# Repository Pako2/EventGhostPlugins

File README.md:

# [EventGhost](http://www.eventghost.net/) plugins.

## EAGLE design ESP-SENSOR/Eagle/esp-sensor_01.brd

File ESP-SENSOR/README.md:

# ESP-SENSOR - Temperaure & humidity sensor and remote-controlled electrical socket
This project is basically the same as the [ESP-SOCKET](https://github.com/Pako2/EventGhostPlugins/tree/master/ESP-SOCKET) project. The difference is only that a temperature and humidity sensor HTU-21D has been added.
Therefore, the original text [README.md](https://github.com/Pako2/EventGhostPlugins/tree/master/ESP-SOCKET/README.md) is fully valid also for this project (only the word "SENSOR" must be used everywhere instead of "SOCKET").

## Initial requirements
I realized that the potential of ESP8266 is very little used in the [ESP-SOCKET](https://github.com/Pako2/EventGhostPlugins/tree/master/ESP-SOCKET) project and that it should be very easy to use it more.
As a first possibility of improvement I was thinking of adding some sensor. I had the HTU-21D sensor at home, so it was the simplest thing for me to add the HTU-21D sensor.
Eventghost plugin should allow to set any number of significant levels.
If any of the levels are exceeded (and / or the value drops below), the corresponding event should be triggered.
A change of relay state must trigger an event in EventGhost too.

### What You Will Need 
### Hardware
An ESP-12 module with at least 32Mbit Flash (equals to 4MBytes)  
A HTU-21D module.

### Software
In contrast to the [ESP-SOCKET](https://github.com/Pako2/EventGhostPlugins/tree/master/ESP-SOCKET) project, one additional library was needed here:
* [HTU21D](https://github.com/enjoyneering/)  - an Arduino library for SHT21, HTU21D & Si70xx written by enjoyneering79

## How the development went
As can be seen from the pictures, this time I worked in two steps:  

1) The breadboard construction (I just added the HTU-21D module to a previously prepared breadboard)
2) Newly designed printed circuit board

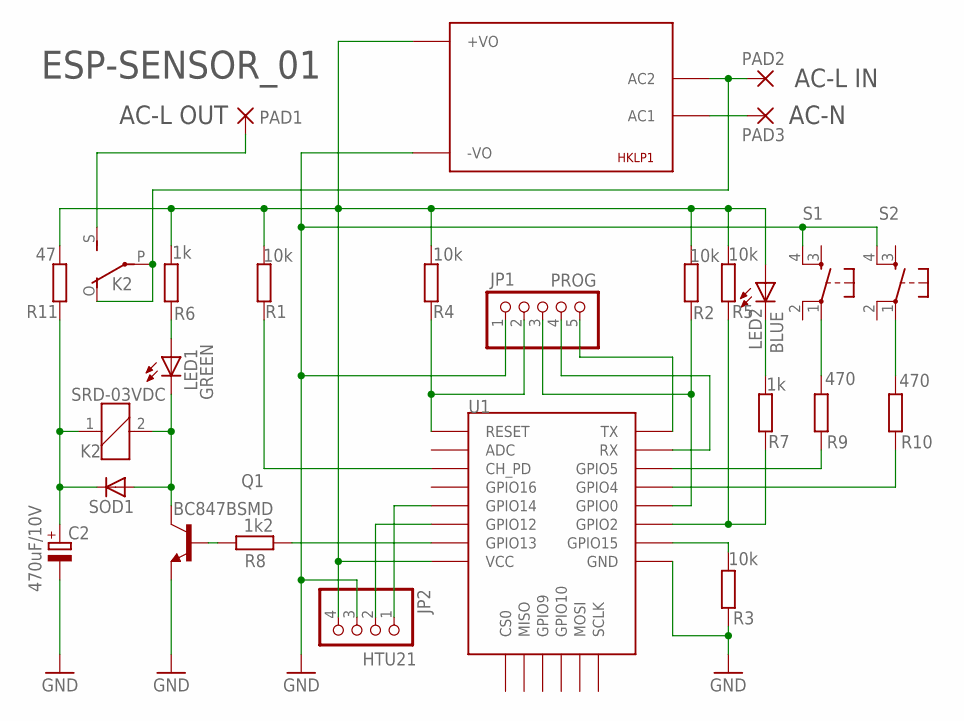
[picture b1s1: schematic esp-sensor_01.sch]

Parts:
C2: 470uF/10V; E3,5-8-B
HKLP1: HKLPM01
JP1: PROG; 1X05-2B
JP2: HTU21; 1X04
K2: SRD-03VDC; G5L-2B
LED1: GREEN; LED3MM-B
LED2: BLUE; LED3MM-B
PAD1, PAD2, PAD3: 3,17/1,1
Q1: BC847BSMD; SOT23
R1, R2, R3, R4, R5: 10k; M1206
R6, R7: 1k; M1206
R8: 1k2; M1206
R9, R10: 470; M1206
R11: 47; 0207/10-2B
S1, S2: DTS-6-B
SOD1: DIODE-MELF-MLL41; MELF-MLL41
U1: ESP12ESMD; ESP12E-SMD

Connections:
3V3: HKLP1.P$4 (+VO), JP2.4, LED2.A, R1.2, R2.2, R4.2, R5.2, R6.2, R11.2, U1.VCC
GND: C2.-, HKLP1.P$3 (-VO), JP1.1, JP2.3, Q1.2 (E), R3.1, S1.4, S2.4, U1.GND
unnamed: Q1.1 (B), R8.2
unnamed: C2.+, K2.1, R11.1, SOD1.C
unnamed: R8.1, U1.GPIO13
unnamed: K2.2, LED1.K (C), Q1.3 (C), SOD1.A
unnamed: R1.1, U1.CH_PD
unnamed: HKLP1.P$2 (AC2), K2.O, K2.P, PAD2.1
unnamed: K2.S, PAD1.1
unnamed: R5.1, R7.1, U1.GPIO2
unnamed: R3.2, U1.GPIO15
unnamed: JP1.2, R4.1, U1.RESET
unnamed: R9.1, S1.1
unnamed: R10.1, S2.1
unnamed: LED2.K (C), R7.2
unnamed: LED1.A, R6.1
unnamed: JP1.3, R2.1, U1.GPIO0
unnamed: JP1.5, U1.TXD0 (TX)
unnamed: R9.2, U1.GPIO5
unnamed: R10.2, U1.GPIO4
unnamed: JP1.4, U1.RXD0 (RX)
unnamed: HKLP1.P$1 (AC1), PAD3.1
unnamed: JP2.2, U1.GPIO12
unnamed: JP2.1, U1.GPIO14

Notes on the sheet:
AC-L IN
AC-L OUT
ESP-SENSOR_01
AC-N

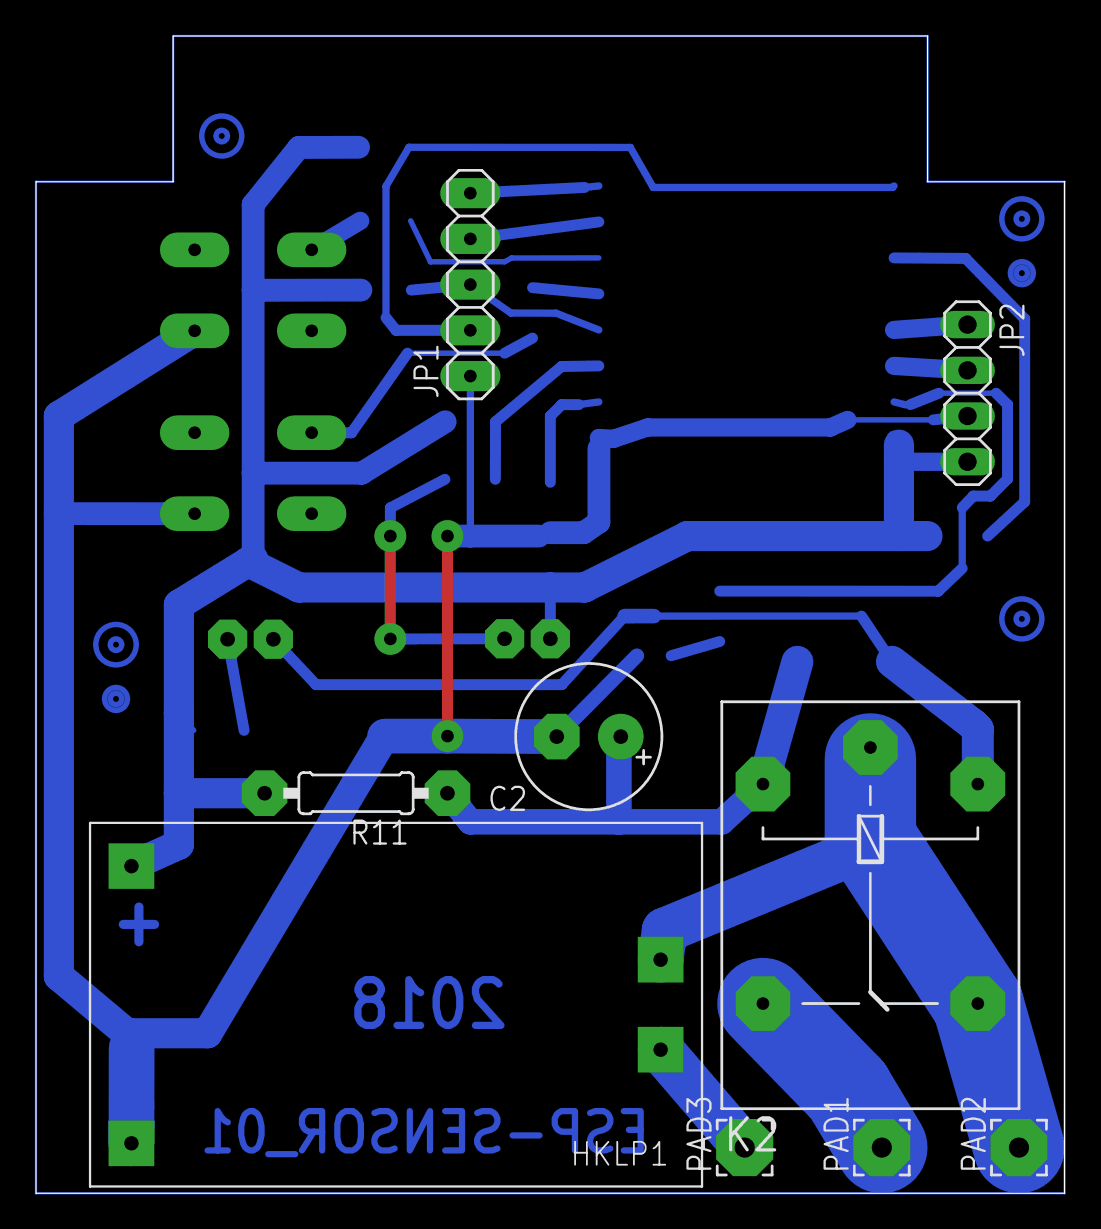
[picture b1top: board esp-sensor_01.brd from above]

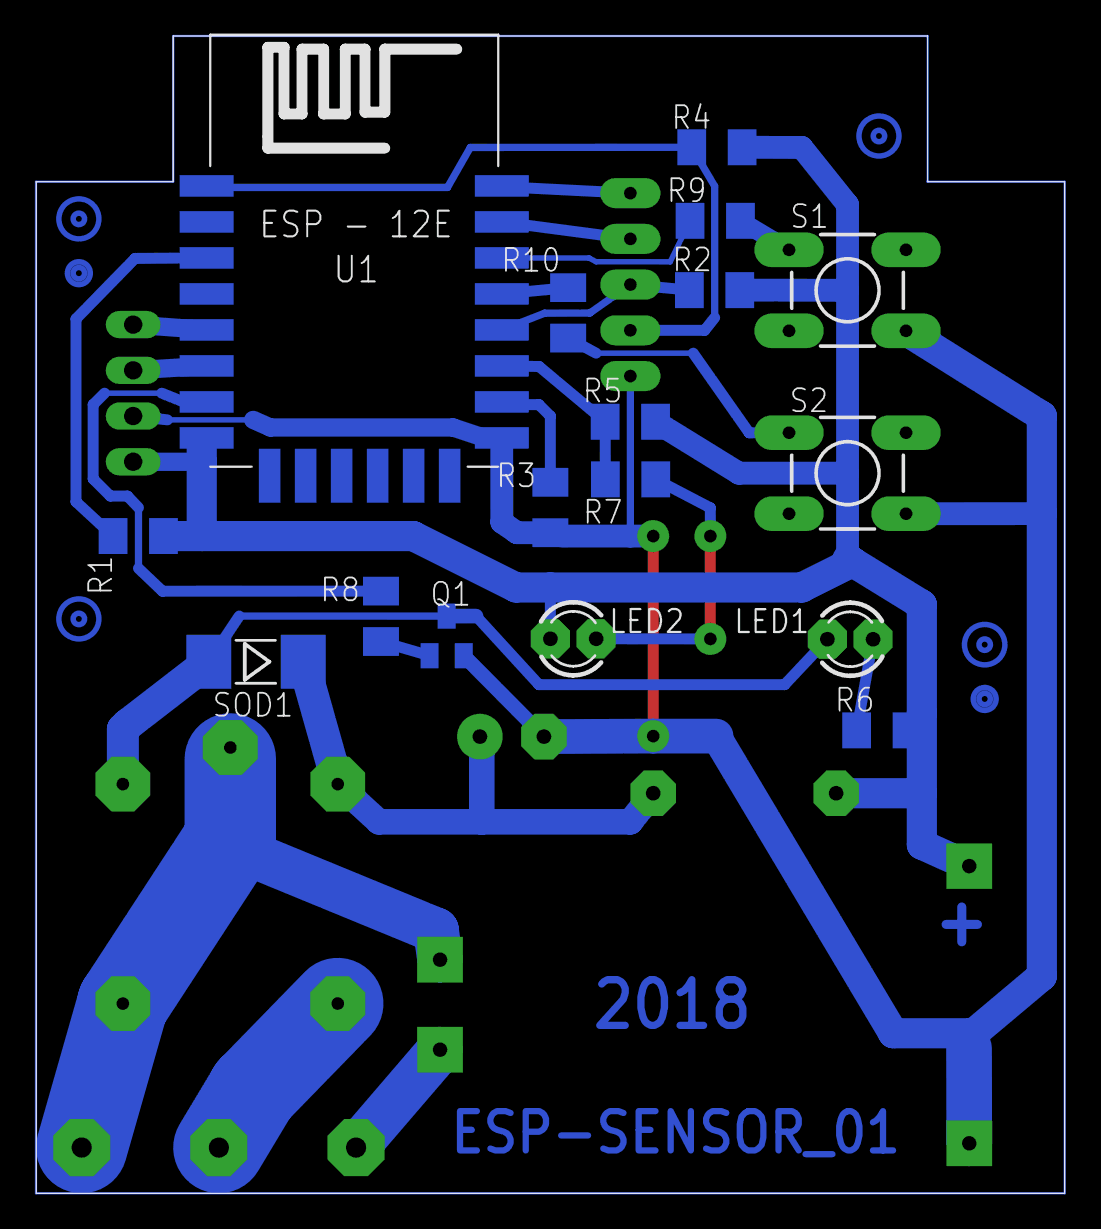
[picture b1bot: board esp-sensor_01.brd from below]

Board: 2 copper layers, 57.1 x 64.3 mm, 26 parts (17 on the bottom side), 24 nets.

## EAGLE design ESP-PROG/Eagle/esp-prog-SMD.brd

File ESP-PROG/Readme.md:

# ESP-PROG  (ESP8266 flasher)
This is not an EventGhost plugin !!!

## Preface
Modules such as **NodeMCU V1.0** or **WeMos D1 mini** are great in the development phase and in many cases even as the ultimate solution. Sometimes, however, it is better to use only a "bare" module, such as ESP-12F.
In this case, it is necessary to resolve how we will upload the firmware to the module (which is built into the new device). One of the possible solutions is described in this article.

## Initial requirements
When I started with the development, I gave myself a simple input condition: flashing should be completely automatic (no push buttons). *The module with the connected programmer should behave the same way as NodeMCU (or WeMos D1 mini).*

## Solution
So I studied the NodeMCU V1.0 circuit diagram and I found it quite simple. It was obvious that I will need some USB converter that also has the RTS signal in addition to the DTR signal. Fortunately, it was not hard to find the right type. Moreover, it is quite cheap (I found a seller with a price just a little over one dollar).  

### Flasher schematic:

### Test version:

### Final version with USB converter:

### Finished programmer in a box and with a cable

### Programmer connected to the target board

## Conclusion
The finished programmer works as expected.  
In the Arduino environment, choose the **NodeMCU 1.0 (ESP-12E Module)** board.  
The programmer works reliably even at the highest speed (**921600**) !  
The target plate must be equipped with a corresponding five-pin connector (see the [ESP-SOCKET](https://github.com/Pako2/EventGhostPlugins/tree/master/ESP-SOCKET) project for example).

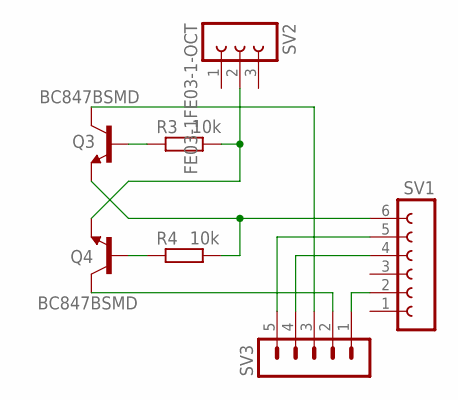
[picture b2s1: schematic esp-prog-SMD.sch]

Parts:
Q3, Q4: BC847BSMD; SOT23
R3, R4: 10k; R1206
SV1: FE06-1; FE06
SV2: FE03-1FE03-1-OCT; FE03-1-OCT
SV3: MA05-1

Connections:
unnamed: Q3.1 (B), R3.1
unnamed: Q4.1 (B), R4.1
unnamed: SV1.2, SV3.1
unnamed: SV1.5, SV3.5
unnamed: SV1.4, SV3.4
unnamed: Q3.2 (E), R4.2, SV1.6
unnamed: Q4.2 (E), R3.2, SV2.2
unnamed: Q4.3 (C), SV3.2
unnamed: Q3.3 (C), SV3.3

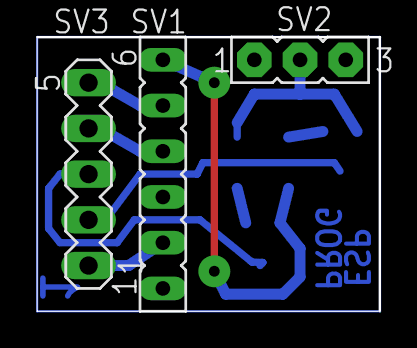
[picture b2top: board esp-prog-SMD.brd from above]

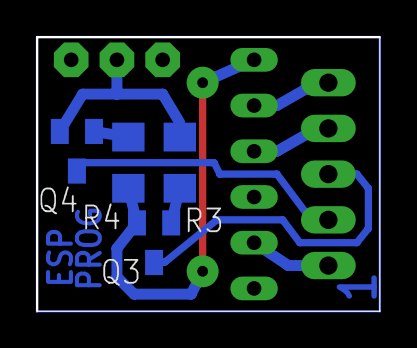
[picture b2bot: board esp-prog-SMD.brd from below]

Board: 2 copper layers, 19.0 x 15.2 mm, 7 parts (4 on the bottom side), 9 nets.

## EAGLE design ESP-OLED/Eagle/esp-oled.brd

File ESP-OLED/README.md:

# ESP-OLED - Remote display for EventGhost
The project assumes the use of ESP-12 module either as **NodeMcu 1.0** or **WeMos D1 mini**.

## Preface
This project is based on my project [ESP-IO-BBT](https://github.com/Pako2/EventGhostPlugins/tree/master/ESP-IO-BBT).
*So, here too we can say:*
The device may be in a completely different network than EventGhost.
Only Internet connectivity at both ends is a condition.
No public IP or VPN or port redirection is required.
**This is possible thanks to the [Beebotte](https://beebotte.com) service.**

## Initial requirements
The basic requirement was a smooth collaboration with EventGhost. This means that the content of the display can be changed using the EventGhost action.
With a web interface, it must be possible the entire device to configure.

## Features
* Max. message length: 300 characters
* Possibility to repeat the last and also the last but one message
* Three buttons to invoke event in EventGhost
* Optional playback of a sound when connecting to a wifi and when a new message is received
* Using WebSocket protocol to exchange data between Hardware and Web Browser
* Using Beebotte/MQTT protocol to exchange data between Hardware and EventGhost
* Data is encoded as JSON object
* Bootstrap for beautiful Web Pages for both Mobile and Desktop Screens
* Thanks to ESPAsyncWebServer Library communication is asynchronous

## Getting Started
This project still in its development phase.
Latest development version is 0.0.1

### What You Will Need 
### Hardware
* A development board like **WeMos D1 mini** or **NodeMcu 1.0** with at least 32Mbit Flash (equals to 4MBytes).
* OLED display 0,96" 128x64 (I2C version)
* Tact switches - 3 pieces
* Resistor 470 ohm - 3 pieces
* Resistor 4700 ohm
* NPN transistor BC247
* Magnetic buzzer CEM-1203(42)

### Software

#### Building From Source
Please install Arduino IDE if you didn't already, then add ESP8266 Core (**Beware! [Install Git Version](https://github.com/esp8266/Arduino#using-git-version)**) on top of it. Additional Library download links are listed below:

* [Arduino IDE](http://www.arduino.cc) - The development IDE
* [ESP8266 Core for Arduino IDE](https://github.com/esp8266/Arduino) - ESP8266 Core
* [ESPAsyncWebServer](https://github.com/me-no-dev/ESPAsyncWebServer) - Asyncrone Web Server with WebSocket Plug-in
* [ESPAsyncTCP](https://github.com/me-no-dev/ESPAsyncTCP) - Mandatory for ESPAsyncWebServer
* [ArduinoJson](https://github.com/bblanchon/ArduinoJson) - JSON Library for Arduino IDE
* [NTPClientLib](https://github.com/gmag11/NtpClient/) - NTP Client Library for Arduino IDE
* [TimeLib](https://github.com/PaulStoffregen/Time) - Mandatory for NTP Client Library
* [PubSubClient](https://github.com/knolleary/pubsubclient) - A client library that provides support for MQTT
* [brzo_i2c](https://github.com/pasko-zh/brzo_i2c) - A fast I2C Implementation written in Assembly for the esp8266
* [SSD1306Brzo](https://github.com/squix78/esp8266-oled-ssd1306/blob/master/SSD1306Brzo.h) - Driver for the SSD1306 and SH1106 based 128x64 pixel OLED display running on the Arduino/ESP8266 platform

**You also need to upload web files to your ESP with ESP8266FS Uploader.**

* [ESP8266FS Uploader](https://github.com/esp8266/arduino-esp8266fs-plugin) - Arduino ESP8266 filesystem uploader

Unlisted libraries are part of ESP8266 Core for Arduino IDE, so you don't need to download them.

### Steps
* First, flash firmware 
* Flash webfiles data to SPIFFS either using ESP8266FS Uploader tool or with your favourite flash tool 
* (optional) Fire up your serial monitor to get informed
* Power on your ESP
* Search for Wireless Network "ESP-OLED" and connect to it (It should be an open network and does not reqiure password)
* Open your browser and type either "http://192.168.4.1" or "http://esp-oled.local" (.local needs Bonjour installed on your computer) on address bar.
* Log on to ESP, default password is "admin"
* Go to "Settings" page
* Configure your amazing access control device. Push "Scan" button to join your wireless network, configure inputs and outputs.
* Save settings, when rebooted your ESP will try to join your wireless network.
* Check your new IP address from serial monitor and connect to your ESP again. (You can also connect to "http://esp-oled.local")
* Congratulations, everything went well, if you encounter any issue feel free to ask help on GitHub.

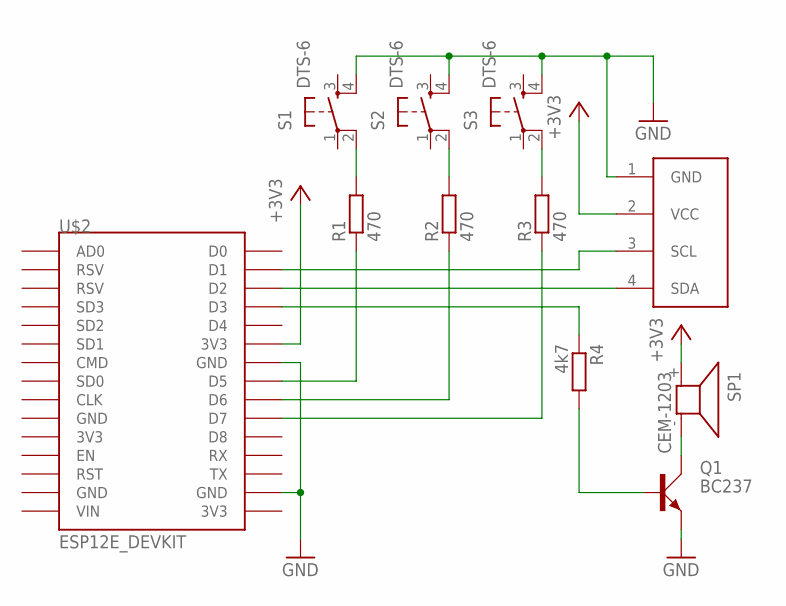
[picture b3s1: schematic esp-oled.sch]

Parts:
Q1: BC237; SOT54A
R1, R2, R3: 470; 0207/10B
R4: 4k7; 0207/10B
S1, S2, S3: DTS-6
SP1: CEM-1203; KSS1201
U$1: I2C_OLED; I2C_OLED_PACKAGE
U$2: ESP12E_DEVKIT

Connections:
+3V3: SP1.+ (1), U$1.2 (VCC), U$2.3V3@1 (3V3)
GND: Q1.E, S1.4, S2.4, S3.4, U$1.1 (GND), U$2.GND@2 (GND), U$2.GND@3 (GND)
unnamed: R1.1, U$2.D5
unnamed: R2.1, U$2.D6
unnamed: R3.1, U$2.D7
unnamed: R1.2, S1.2
unnamed: R2.2, S2.2
unnamed: R3.2, S3.2
unnamed: U$1.4 (SDA), U$2.D2
unnamed: U$1.3 (SCL), U$2.D1
unnamed: R4.1, U$2.D3
unnamed: Q1.C, SP1.- (2)
unnamed: Q1.B, R4.2

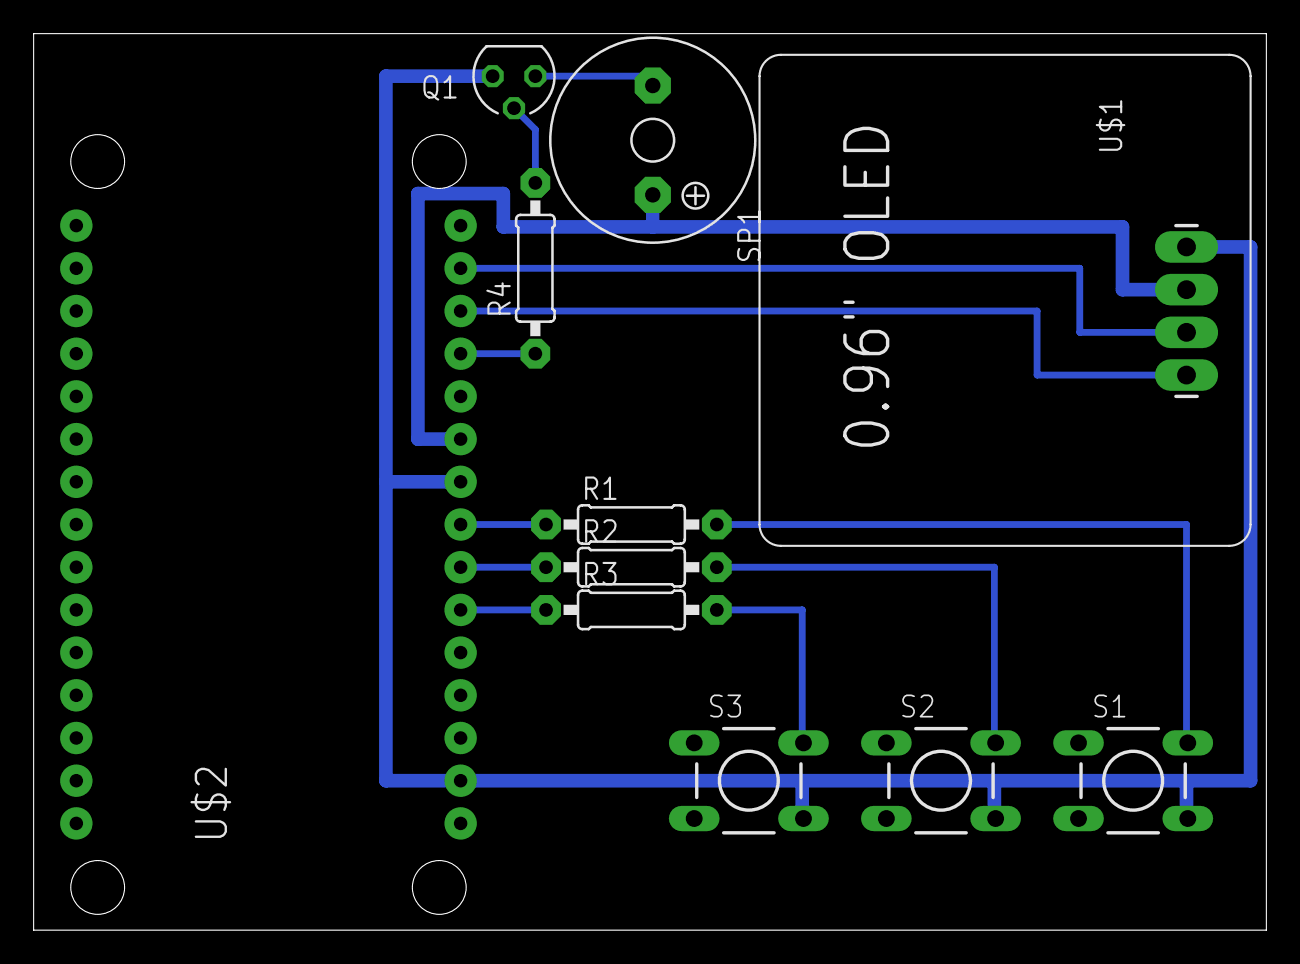
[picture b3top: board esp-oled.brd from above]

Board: 2 copper layers, 73.3 x 53.3 mm, 11 parts (0 on the bottom side), 13 nets.

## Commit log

2017-02-20 Create dummy
2017-07-03 Add files via upload
    Version 0.1
    Added support for RF125-PS module.
2017-07-17 Add files via upload
    bugfix
2017-09-17 changes to increase reliability
2017-09-23 bugfix
2017-09-23 0.0.3
2017-09-24 Creating the ESP-IO-BBT folder in the repository
2017-09-25 0.0.1
2017-11-12 0.0.2
2017-11-13 0.0.4
2017-11-18 0.0.0
2018-01-03 Create README.md
    0.0.1
2018-01-03 Create BeebotteChannel.png
    0.0.1
2018-03-21 Create control.htm
    0.0.1
